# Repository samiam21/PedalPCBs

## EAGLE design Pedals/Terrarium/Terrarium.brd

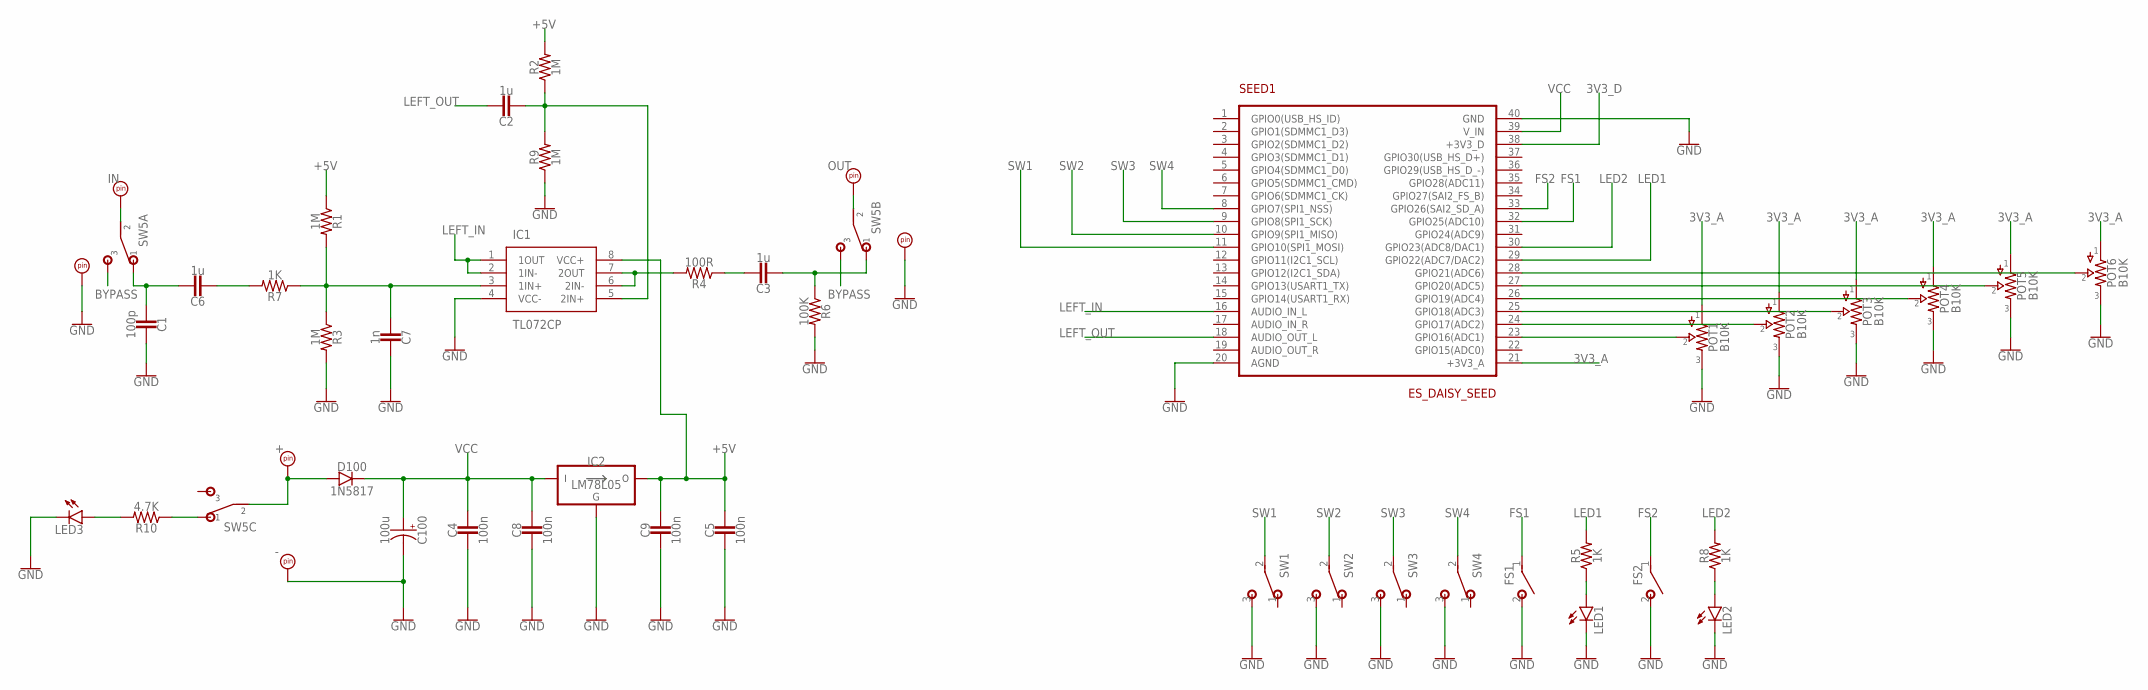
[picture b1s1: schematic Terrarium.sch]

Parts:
C1: 100p; 5MM
C2, C3, C6: 1u; .33UF+
C4, C5, C8, C9: 100n; 5MM
C7: 1n; 5MM
C100: 100u; 050_2.5MM.2
D100: 1N5817; DO41-3
FS1, FS2: SPST
GND: PADRD; UNLABELED
IC1: TL072CP; DIP794W53P254L959H508Q8N
IC2: LM78L05; TO92-
IN: PADRD; UNLABELED
IN_GND: PADRD; UNLABELED
LED1, LED2, LED3: LED.3; 3MM_2
OUT: PADRD; UNLABELED
OUT_GND: PADRD; UNLABELED
POT1, POT2, POT3, POT4, POT5, POT6: B10K; 16MM_PADS.2
PWR: PADRD; UNLABELED
R1, R2, R3, R9: 1M; 7.5MM.2
R4: 100R; 7.5MM.2
R5, R7, R8: 1K; 7.5MM.2
R6: 100K; 7.5MM.2
R10: 4.7K; 7.5MM.2
SEED1: ES_DAISY_SEED
SW1, SW2, SW3, SW4: SPDT.1; SPDT_SOLDER_LUG
SW5: 3PDTTOGGLE; 3PDT2

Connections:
3V3_A: POT1.1, POT2.1, POT3.1, POT4.1, POT5.1, POT6.1, SEED1.21 (+3V3_A)
3V3_D: SEED1.38 (+3V3_D)
+5V: C5.1, C9.1, IC1.8 (VCC+), IC2.3 (VO), R1.1, R2.2
BYPASS: SW5.A3 (3), SW5.B3 (3)
FS1: FS1.1, SEED1.32 (GPIO25(ADC10))
FS2: FS2.1, SEED1.33 (GPIO26(SAI2_SD_A))
GND: C1.1, C4.2, C5.2, C7.1, C8.2, C9.2, C100.-, FS1.2 (S), FS2.2 (S), GND.P$1, IC1.4 (VCC-), IC2.2 (GND), IN_GND.P$1, LED1.P$1 (C), LED2.P$1 (C), LED3.P$1 (C), OUT_GND.P$1, POT1.3, POT2.3, POT3.3, POT4.3, POT5.3, POT6.3, R3.2, R6.2, R9.1, SEED1.20 (AGND), SEED1.40 (GND), SW1.3 (S), SW2.3 (S), SW3.3 (S), SW4.3 (S)
LED1: R5.2, SEED1.29 (GPIO22(ADC7/DAC2))
LED2: R8.2, SEED1.30 (GPIO23(ADC8/DAC1))
LEFT_IN: IC1.1 (1OUT), IC1.2 (1IN-), SEED1.16 (AUDIO_IN_L)
LEFT_OUT: C2.1, SEED1.18 (AUDIO_OUT_L)
unnamed: POT1.2, SEED1.23 (GPIO16(ADC1))
unnamed: POT2.2, SEED1.24 (GPIO17(ADC2))
unnamed: POT3.2, SEED1.25 (GPIO18(ADC3))
unnamed: POT4.2, SEED1.26 (GPIO19(ADC4))
unnamed: POT5.2, SEED1.27 (GPIO20(ADC5))
unnamed: POT6.2, SEED1.28 (GPIO21(ADC6))
unnamed: LED1.ANODE (A), R5.1
unnamed: LED2.ANODE (A), R8.1
unnamed: D100.A, PWR.P$1, SW5.C2 (2)
unnamed: C3.1, R4.1
unnamed: C3.2, R6.1, SW5.B1 (1)
unnamed: C1.2, C6.1, SW5.A1 (1)
unnamed: IN.P$1, SW5.A2 (2)
unnamed: IC1.6 (2IN-), IC1.7 (2OUT), R4.2
unnamed: C6.2, R7.2
unnamed: C7.2, IC1.3 (1IN+), R1.2, R3.1, R7.1
unnamed: C2.2, IC1.5 (2IN+), R2.1, R9.2
unnamed: R10.1, SW5.C1 (1)
unnamed: LED3.ANODE (A), R10.2
unnamed: OUT.P$1, SW5.B2 (2)
SW1: SEED1.11 (GPIO10(SPI1_MOSI)), SW1.2
SW2: SEED1.10 (GPIO9(SPI1_MISO)), SW2.2
SW3: SEED1.9 (GPIO8(SPI1_SCK)), SW3.2
SW4: SEED1.8 (GPIO7(SPI1_NSS)), SW4.2
VCC: C4.1, C8.1, C100.+, D100.C, IC2.1 (VI), SEED1.39 (V_IN)

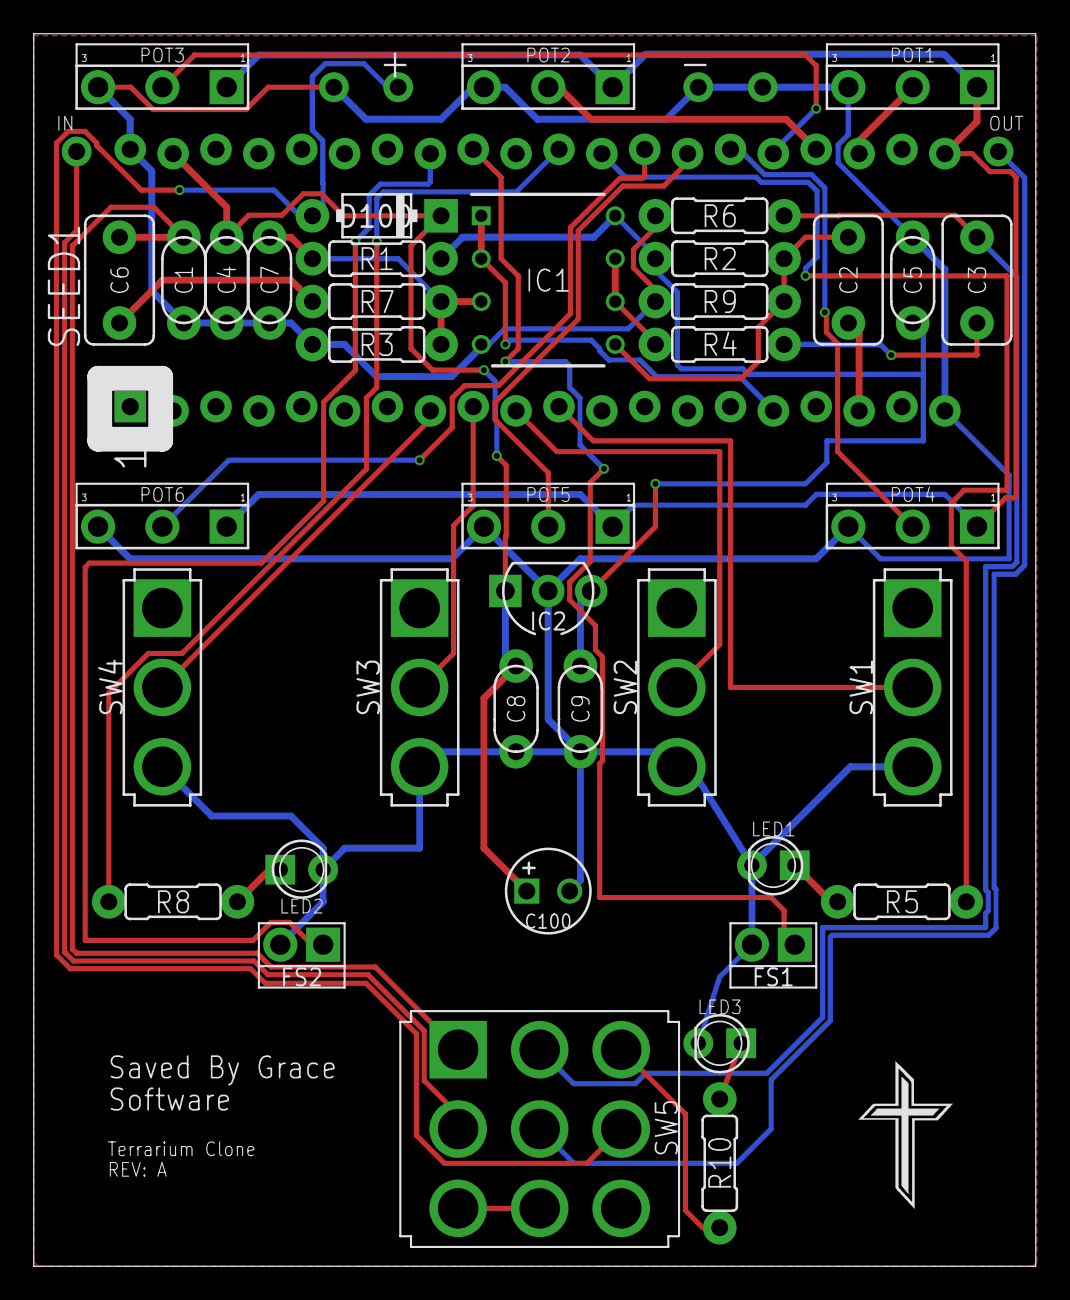
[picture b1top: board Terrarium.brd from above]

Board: 2 copper layers, 59.4 x 73.0 mm, 46 parts (0 on the bottom side), 35 nets.

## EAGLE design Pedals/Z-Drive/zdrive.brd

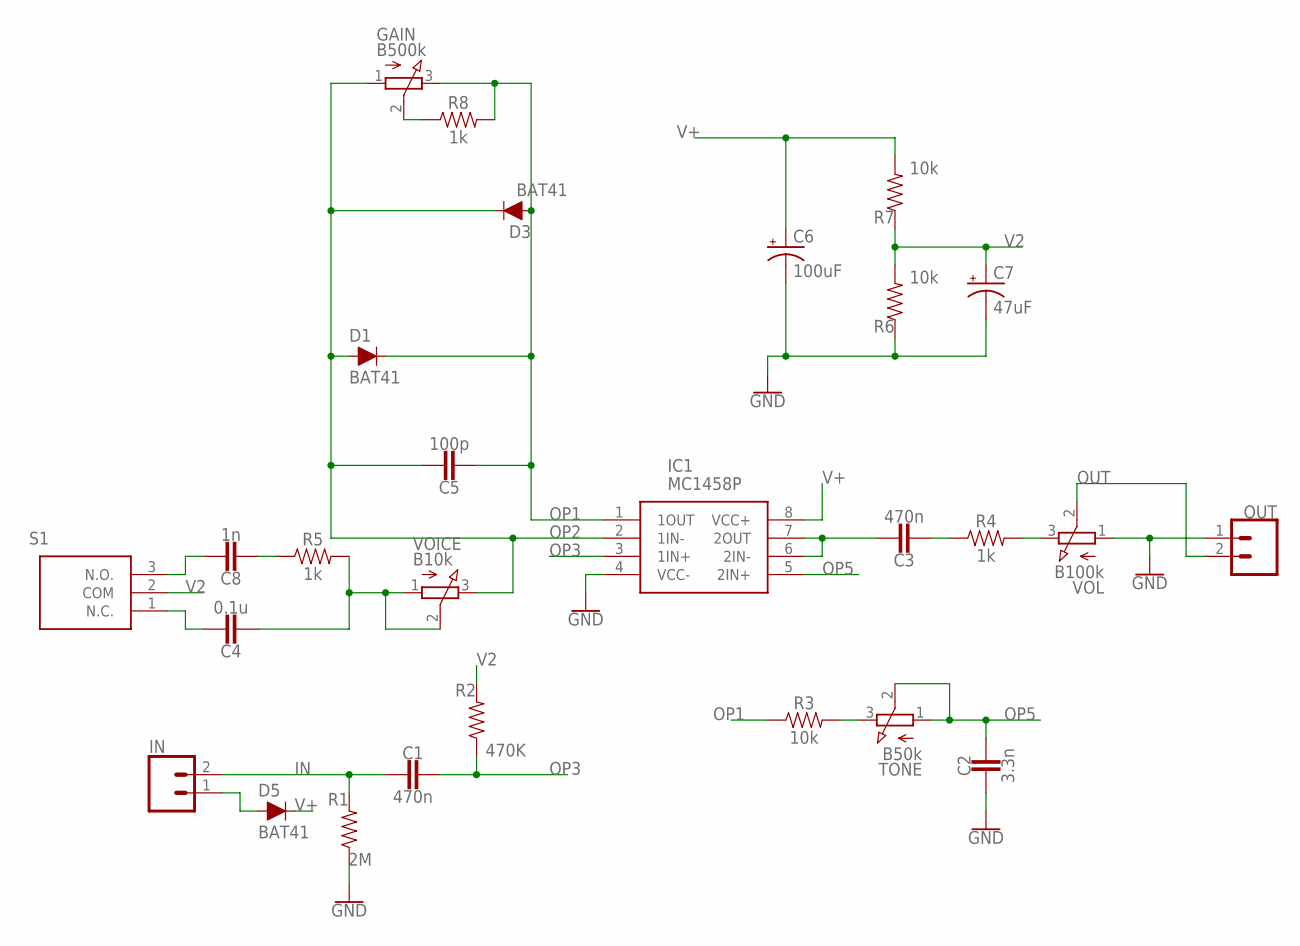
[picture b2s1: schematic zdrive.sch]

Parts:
C1, C3: 470n; .33UF+
C2: 3.3n; .33UF+
C4: 0.1u; .33UF+
C5: 100p; .33UF+
C6: 100uF; CPOL-RADIAL-2.5MM-6.5MM
C7: 47uF; CPOL-RADIAL-2.5MM-6.5MM
C8: 1n; .33UF+
D1, D3, D5: BAT41; DIODE-1N4001-KIT
GAIN: B500k; 3RP/1610N
IC1: MC1458P; DIP794W53P254L959H508Q8N
IN: CONN_02; 1X02
OUT: CONN_02; 1X02
R1: 2M; AXIAL-0.3
R2: 470K; AXIAL-0.3
R3, R6, R7: 10k; AXIAL-0.3
R4, R5, R8: 1k; AXIAL-0.3
S1: 100SP1T1B2M2QE; 100SP1T1B4M2QE
TONE: B50k; 3RP/1610N
VOICE: B10k; 3RP/1610N
VOL: B100k; 3RP/1610N

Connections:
9V: D5.A, IN.1
GND: C2.2, C6.2 (-), C7.2 (-), IC1.4 (VCC-), OUT.1, R1.P$1 (1), R6.P$1 (1), VOL.1 (A)
IN: C1.2, IN.2, R1.P$2 (2)
unnamed: R3.P$2 (2), TONE.3 (E)
unnamed: C3.1, IC1.6 (2IN-), IC1.7 (2OUT)
unnamed: C3.2, R4.P$1 (1)
unnamed: R4.P$2 (2), VOL.3 (E)
unnamed: GAIN.2 (S), R8.P$1 (1)
unnamed: C8.2, R5.P$1 (1)
unnamed: C4.1, S1.1 (N.C.)
unnamed: C8.1, S1.3 (N.O.)
unnamed: C4.2, R5.P$2 (2), VOICE.1 (A), VOICE.2 (S)
OP1: C5.2, D1.C, D3.A, GAIN.3 (E), IC1.1 (1OUT), R3.P$1 (1), R8.P$2 (2)
OP2: C5.1, D1.A, D3.C, GAIN.1 (A), IC1.2 (1IN-), VOICE.3 (E)
OP3: C1.1, IC1.3 (1IN+), R2.P$1 (1)
OP5: C2.1, IC1.5 (2IN+), TONE.1 (A), TONE.2 (S)
OUT: OUT.2, VOL.2 (S)
V2: C7.1 (+), R2.P$2 (2), R6.P$2 (2), R7.P$1 (1), S1.2 (COM)
V+: C6.1 (+), D5.C, IC1.8 (VCC+), R7.P$2 (2)

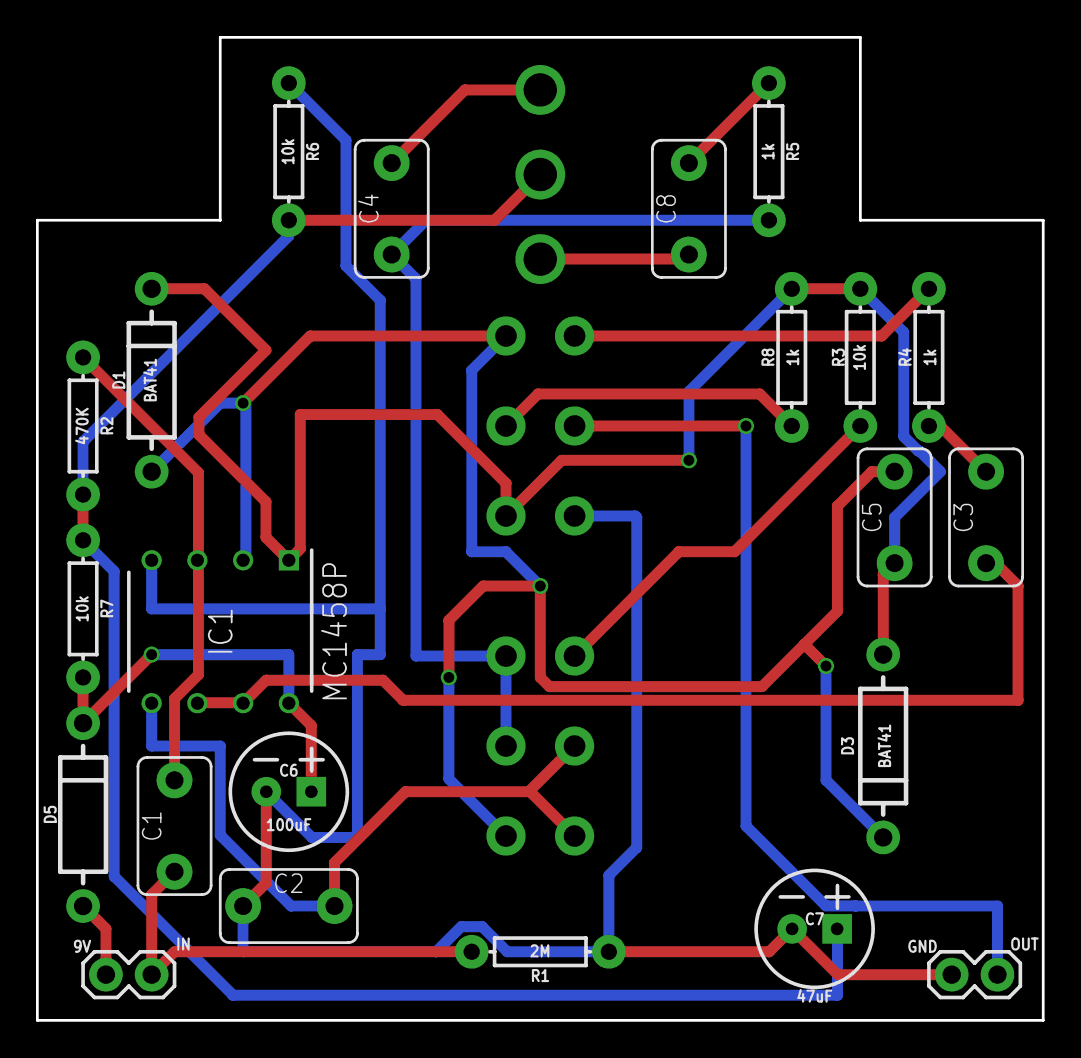
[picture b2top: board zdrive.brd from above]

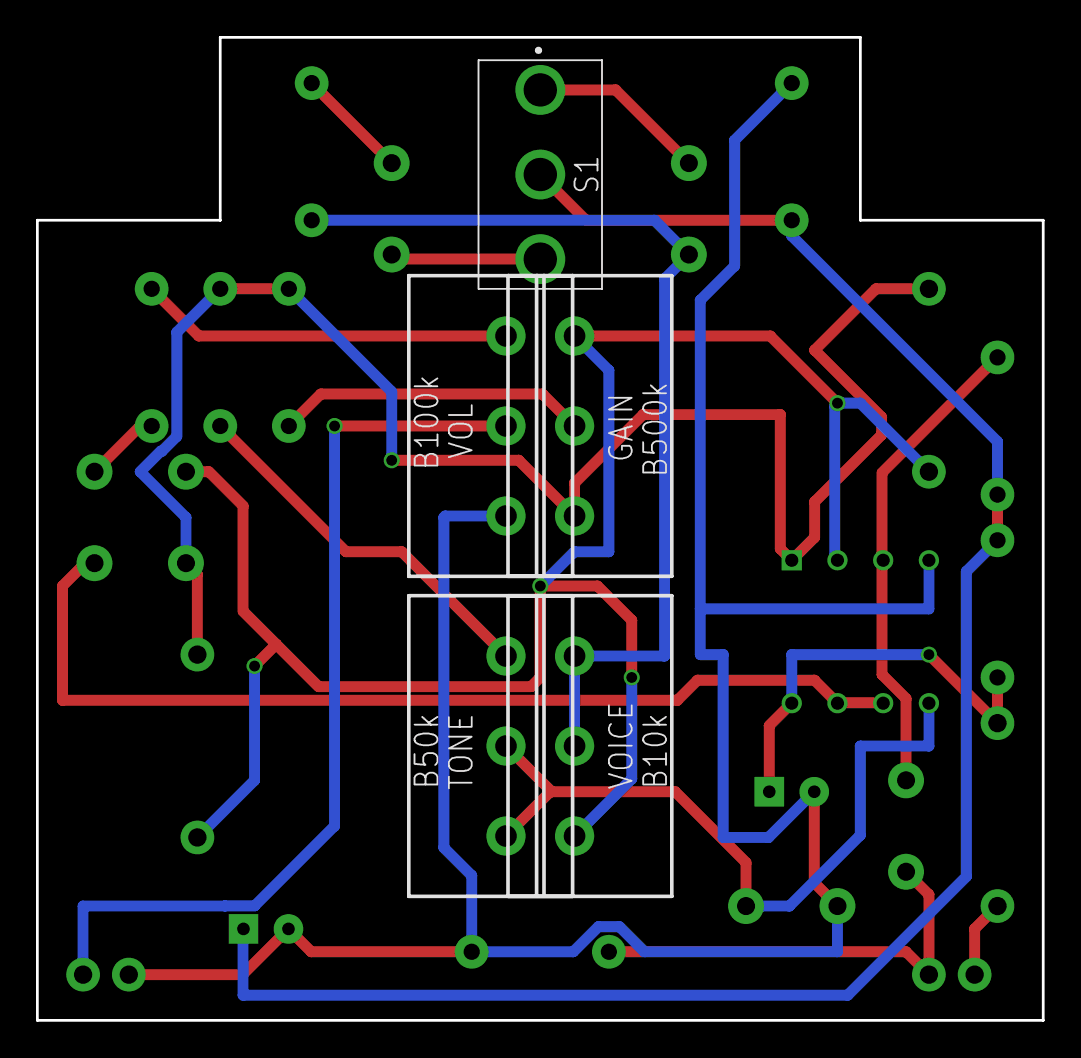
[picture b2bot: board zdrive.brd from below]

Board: 2 copper layers, 55.9 x 54.6 mm, 27 parts (5 on the bottom side), 19 nets.

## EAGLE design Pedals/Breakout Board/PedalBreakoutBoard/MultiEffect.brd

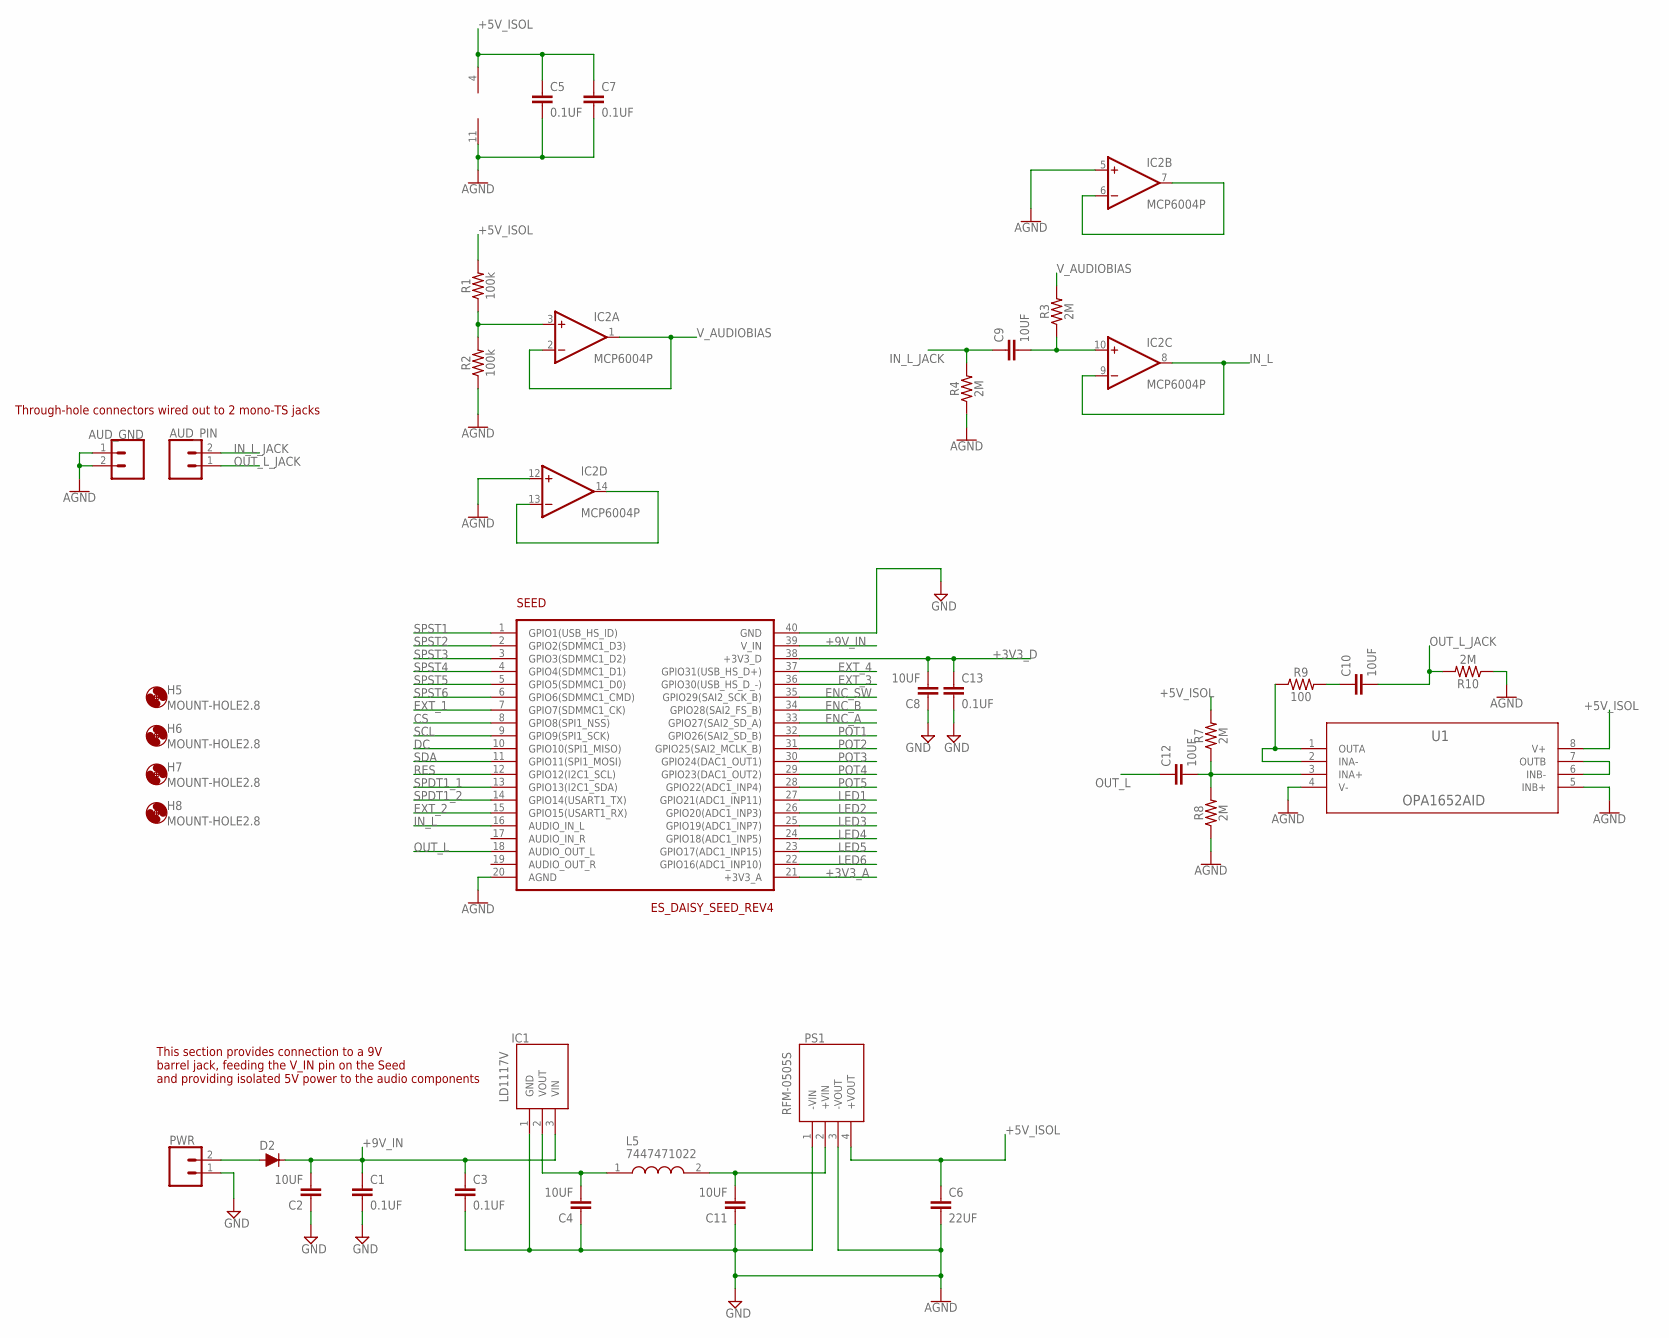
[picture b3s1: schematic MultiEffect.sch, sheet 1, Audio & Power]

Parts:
AUD_GND: CONN_02; 1X02
AUD_PIN: CONN_02; 1X02
C1, C3, C5, C7, C13: 0.1UF; CAP-PTH-SMALL-KIT
C2, C4, C8, C9, C10, C11, C12: 10UF; CAP-PTH-SMALL-KIT
C6: 22UF; CAP-PTH-SMALL-KIT
D2: 200mA/100V/1V; DIODE-1N4148
H5, H6, H7, H8: MOUNT-HOLE2.8; 2,8
IC1: LD1117V; TO255P460X1020X2008-3P
IC2: MCP6004P; DIL14
L5: 7447471022; WE-TIS_111190
PS1: RFM-0505S; RFM0505S
PWR: CONN_02; 1X02
R1, R2: 100k; AXIAL-0.3
R3, R4, R7, R8, R10: 2M; AXIAL-0.3
R9: 100; AXIAL-0.3
SEED: ES_DAISY_SEED_REV4; ES_DAISY_SEED
U1: OPA1652AID; D8

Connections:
+3V3_A: SEED.21 (+3V3_A); also elsewhere on the board
+3V3_D: C8.2, C13.1, SEED.38 (+3V3_D); also elsewhere on the board
+5V_ISOL: C5.1, C6.1, C7.1, IC2.4 (V+), PS1.4 (+VOUT), R1.P$2 (2), R7.P$2 (2), U1.8 (V+)
+9V_IN: C1.1, C2.2, C3.1, D2.C, IC1.3 (VIN), SEED.39 (V_IN)
AGND: AUD_GND.1, AUD_GND.2, C5.2, C7.2, IC2.5 (+IN), IC2.11 (V-), IC2.12 (+IN), R2.P$1 (1), R4.P$1 (1), R8.P$1 (1), R10.P$1 (1), SEED.20 (AGND), U1.4 (V-), U1.5 (INB+)
CS: SEED.8 (GPIO8(SPI1_NSS)); also elsewhere on the board
DC: SEED.10 (GPIO10(SPI1_MISO)); also elsewhere on the board
ENC_A: SEED.33 (GPIO27(SAI2_SD_A)); also elsewhere on the board
ENC_B: SEED.34 (GPIO28(SAI2_FS_B)); also elsewhere on the board
ENC_SW: SEED.35 (GPIO29(SAI2_SCK_B)); also elsewhere on the board
EXT_1: SEED.7 (GPIO7(SDMMC1_CK)); also elsewhere on the board
EXT_2: SEED.15 (GPIO15(USART1_RX)); also elsewhere on the board
EXT_3: SEED.36 (GPIO30(USB_HS_D_-)); also elsewhere on the board
EXT_4: SEED.37 (GPIO31(USB_HS_D+)); also elsewhere on the board
GND: C1.2, C2.1, C3.2, C4.1, C6.2, C8.1, C11.1, C13.2, IC1.1 (GND), PS1.1 (-VIN), PS1.3 (-VOUT), PWR.1, SEED.40 (GND); also elsewhere on the board
IN_L: IC2.8 (OUT), IC2.9 (-IN), SEED.16 (AUDIO_IN_L)
IN_L_JACK: AUD_PIN.2, C9.1, R4.P$2 (2)
LED1: SEED.27 (GPIO21(ADC1_INP11)); also elsewhere on the board
LED2: SEED.26 (GPIO20(ADC1_INP3)); also elsewhere on the board
LED3: SEED.25 (GPIO19(ADC1_INP7)); also elsewhere on the board
LED4: SEED.24 (GPIO18(ADC1_INP5)); also elsewhere on the board
LED5: SEED.23 (GPIO17(ADC1_INP15)); also elsewhere on the board
LED6: SEED.22 (GPIO16(ADC1_INP10)); also elsewhere on the board
unnamed: D2.A, PWR.2
unnamed: IC2.3 (+IN), R1.P$1 (1), R2.P$2 (2)
unnamed: C11.2, L5.2, PS1.2 (+VIN)
unnamed: C4.2, IC1.2 (VOUT), L5.1
unnamed: C9.2, IC2.10 (+IN), R3.P$1 (1)
unnamed: IC2.13 (-IN), IC2.14 (OUT)
unnamed: C12.2, R7.P$1 (1), R8.P$2 (2), U1.3 (INA+)
unnamed: R9.P$1 (1), U1.1 (OUTA), U1.2 (INA-)
unnamed: C10.1, R9.P$2 (2)
unnamed: U1.6 (INB-), U1.7 (OUTB)
unnamed: IC2.6 (-IN), IC2.7 (OUT)
OUT_L: C12.1, SEED.18 (AUDIO_OUT_L)
OUT_L_JACK: AUD_PIN.1, C10.2, R10.P$2 (2)
POT1: SEED.32 (GPIO26(SAI2_SD_B)); also elsewhere on the board
POT2: SEED.31 (GPIO25(SAI2_MCLK_B)); also elsewhere on the board
POT3: SEED.30 (GPIO24(DAC1_OUT1)); also elsewhere on the board
POT4: SEED.29 (GPIO23(DAC1_OUT2)); also elsewhere on the board
POT5: SEED.28 (GPIO22(ADC1_INP4)); also elsewhere on the board
RES: SEED.12 (GPIO12(I2C1_SCL)); also elsewhere on the board
SCL: SEED.9 (GPIO9(SPI1_SCK)); also elsewhere on the board
SDA: SEED.11 (GPIO11(SPI1_MOSI)); also elsewhere on the board
SPDT1_1: SEED.13 (GPIO13(I2C1_SDA)); also elsewhere on the board
SPDT1_2: SEED.14 (GPIO14(USART1_TX)); also elsewhere on the board
SPST1: SEED.1 (GPIO1(USB_HS_ID)); also elsewhere on the board
SPST2: SEED.2 (GPIO2(SDMMC1_D3)); also elsewhere on the board
SPST3: SEED.3 (GPIO3(SDMMC1_D2)); also elsewhere on the board
SPST4: SEED.4 (GPIO4(SDMMC1_D1)); also elsewhere on the board
SPST5: SEED.5 (GPIO5(SDMMC1_D0)); also elsewhere on the board
SPST6: SEED.6 (GPIO6(SDMMC1_CMD)); also elsewhere on the board
V_AUDIOBIAS: IC2.1 (OUT), IC2.2 (-IN), R3.P$2 (2)

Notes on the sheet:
Through-hole connectors wired out to 2 mono-TS jacks
This section provides connection to a 9V barrel jack, feeding the V_IN pin on the Seed and providing isolated 5V power to the audio components

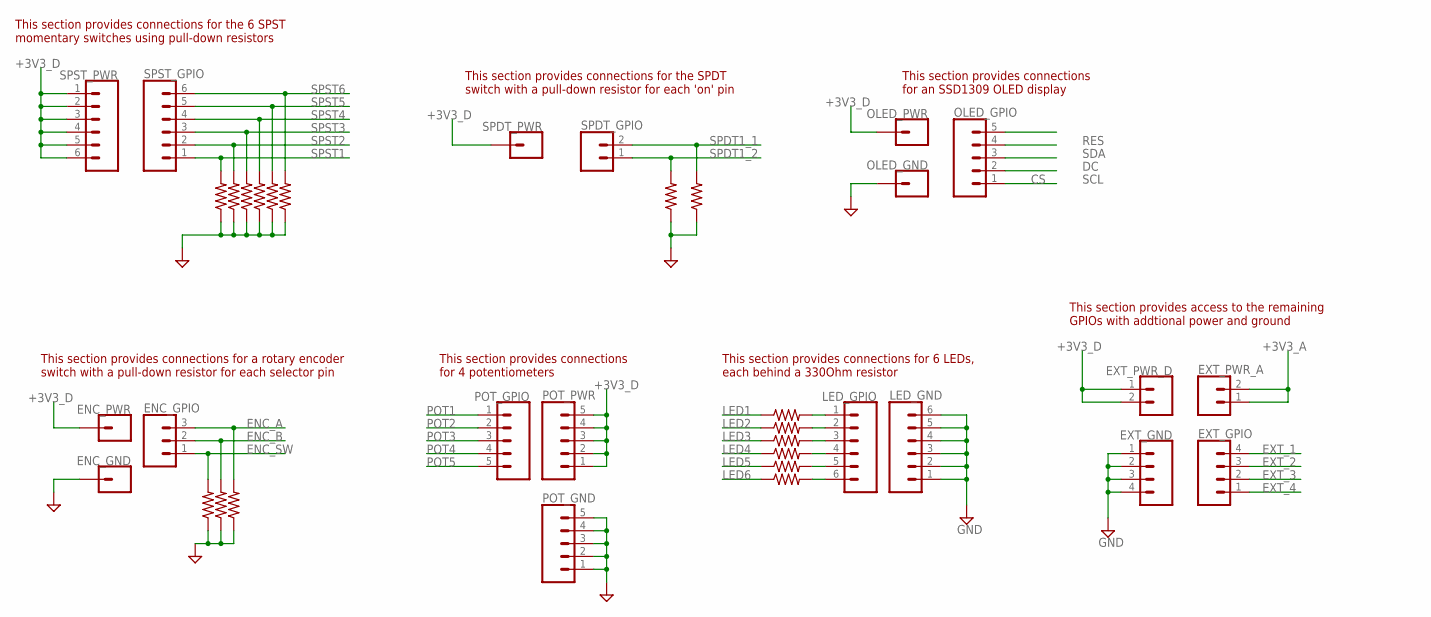
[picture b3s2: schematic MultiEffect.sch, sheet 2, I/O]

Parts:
D11, D12: 10k; AXIAL-0.3
ENC_GND: CONN_01; 1X01
ENC_GPIO: CONN_03; 1X03
ENC_PWR: CONN_01; 1X01
EXT_GND: CONN_04; 1X04
EXT_GPIO: CONN_04; 1X04
EXT_PWR_A: CONN_02; 1X02
EXT_PWR_D: CONN_02; 1X02
H2, H3, H4: 10k; AXIAL-0.3
L1, L2, L3, L4, L6, L7: 330; AXIAL-0.3
LED_GND: CONN_06SILK_FEMALE_PTH; 1X06
LED_GPIO: CONN_06SILK_FEMALE_PTH; 1X06
OLED_GND: CONN_01; 1X01
OLED_GPIO: CONN_05; 1X05
OLED_PWR: CONN_01; 1X01
POT_GND: CONN_05; 1X05
POT_GPIO: CONN_05; 1X05
POT_PWR: CONN_05; 1X05
S1, S2, S3, S4, S5, S6: 10k; AXIAL-0.3
SPDT_GPIO: CONN_02; 1X02
SPDT_PWR: CONN_01; 1X01
SPST_GPIO: CONN_06SILK_FEMALE_PTH; 1X06
SPST_PWR: CONN_06SILK_FEMALE_PTH; 1X06

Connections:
+3V3_A: EXT_PWR_A.1, EXT_PWR_A.2; also elsewhere on the board
+3V3_D: ENC_PWR.1, EXT_PWR_D.1, EXT_PWR_D.2, OLED_PWR.1, POT_PWR.1, POT_PWR.2, POT_PWR.3, POT_PWR.4, POT_PWR.5, SPDT_PWR.1, SPST_PWR.1, SPST_PWR.2, SPST_PWR.3, SPST_PWR.4, SPST_PWR.5, SPST_PWR.6; also elsewhere on the board
CS: OLED_GPIO.1; also elsewhere on the board
DC: OLED_GPIO.3; also elsewhere on the board
ENC_A: ENC_GPIO.3, H4.P$2 (2); also elsewhere on the board
ENC_B: ENC_GPIO.2, H3.P$2 (2); also elsewhere on the board
ENC_SW: ENC_GPIO.1, H2.P$2 (2); also elsewhere on the board
EXT_1: EXT_GPIO.4; also elsewhere on the board
EXT_2: EXT_GPIO.3; also elsewhere on the board
EXT_3: EXT_GPIO.2; also elsewhere on the board
EXT_4: EXT_GPIO.1; also elsewhere on the board
GND: D11.P$1 (1), D12.P$1 (1), ENC_GND.1, EXT_GND.1, EXT_GND.2, EXT_GND.3, EXT_GND.4, H2.P$1 (1), H3.P$1 (1), H4.P$1 (1), LED_GND.1, LED_GND.2, LED_GND.3, LED_GND.4, LED_GND.5, LED_GND.6, OLED_GND.1, POT_GND.1, POT_GND.2, POT_GND.3, POT_GND.4, POT_GND.5, S1.P$1 (1), S2.P$1 (1), S3.P$1 (1), S4.P$1 (1), S5.P$1 (1), S6.P$1 (1); also elsewhere on the board
LED1: L1.P$1 (1); also elsewhere on the board
LED2: L2.P$1 (1); also elsewhere on the board
LED3: L3.P$1 (1); also elsewhere on the board
LED4: L4.P$1 (1); also elsewhere on the board
LED5: L6.P$1 (1); also elsewhere on the board
LED6: L7.P$1 (1); also elsewhere on the board
unnamed: L1.P$2 (2), LED_GPIO.1
unnamed: L2.P$2 (2), LED_GPIO.2
unnamed: L3.P$2 (2), LED_GPIO.3
unnamed: L4.P$2 (2), LED_GPIO.4
unnamed: L6.P$2 (2), LED_GPIO.5
unnamed: L7.P$2 (2), LED_GPIO.6
POT1: POT_GPIO.1; also elsewhere on the board
POT2: POT_GPIO.2; also elsewhere on the board
POT3: POT_GPIO.3; also elsewhere on the board
POT4: POT_GPIO.4; also elsewhere on the board
POT5: POT_GPIO.5; also elsewhere on the board
RES: OLED_GPIO.5; also elsewhere on the board
SCL: OLED_GPIO.2; also elsewhere on the board
SDA: OLED_GPIO.4; also elsewhere on the board
SPDT1_1: D11.P$2 (2), SPDT_GPIO.2; also elsewhere on the board
SPDT1_2: D12.P$2 (2), SPDT_GPIO.1; also elsewhere on the board
SPST1: S1.P$2 (2), SPST_GPIO.1; also elsewhere on the board
SPST2: S2.P$2 (2), SPST_GPIO.2; also elsewhere on the board
SPST3: S3.P$2 (2), SPST_GPIO.3; also elsewhere on the board
SPST4: S4.P$2 (2), SPST_GPIO.4; also elsewhere on the board
SPST5: S5.P$2 (2), SPST_GPIO.5; also elsewhere on the board
SPST6: S6.P$2 (2), SPST_GPIO.6; also elsewhere on the board

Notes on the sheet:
This section provides connections for the SPDT switch with a pull-down resistor for each 'on' pin
This section provides connections for a rotary encoder switch with a pull-down resistor for each selector pin
This section provides connections for 4 potentiometers
This section provides connections for the 6 SPST momentary switches using pull-down resistors
This section provides connections for 6 LEDs, each behind a 330Ohm resistor
This section provides connections for an SSD1309 OLED display
This section provides access to the remaining GPIOs with addtional power and ground

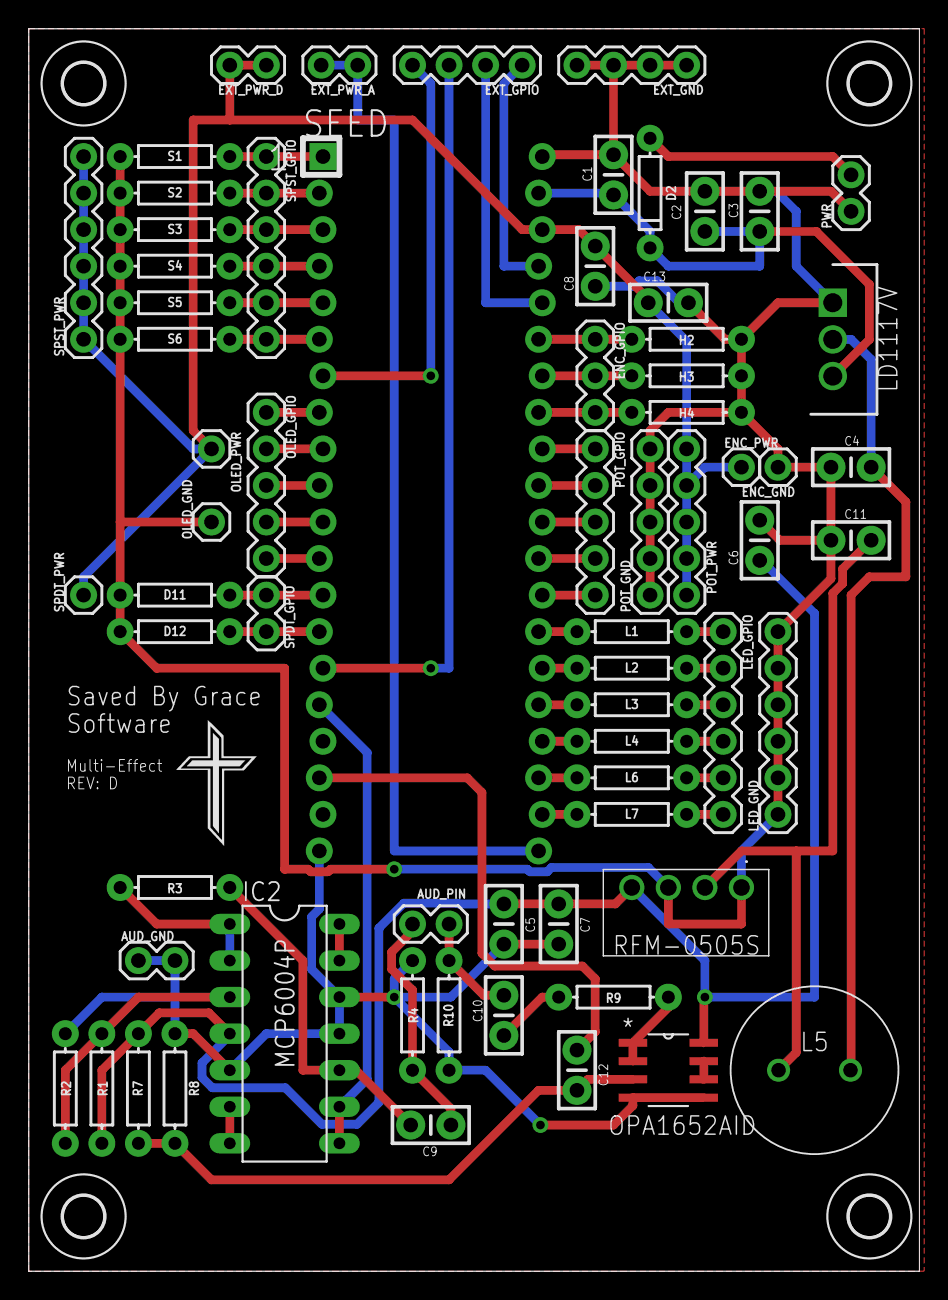
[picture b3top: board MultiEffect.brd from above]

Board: 2 copper layers, 61.9 x 86.3 mm, 71 parts (0 on the bottom side), 59 nets.

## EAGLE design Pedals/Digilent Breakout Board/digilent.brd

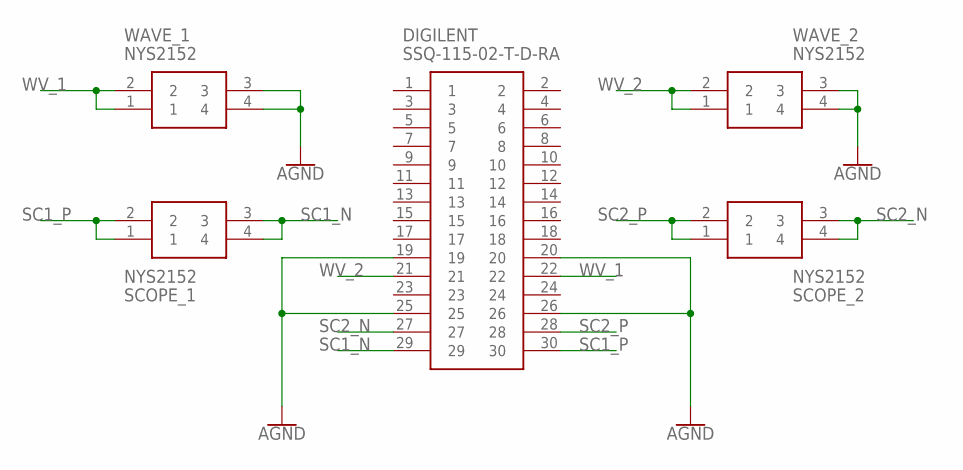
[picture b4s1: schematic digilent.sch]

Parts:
DIGILENT: SSQ-115-02-T-D-RA; RHDRRA30W64P254_2X15_3861X851X
SCOPE_1, SCOPE_2: NYS2152
WAVE_1, WAVE_2: NYS2152

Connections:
AGND: DIGILENT.19, DIGILENT.20, DIGILENT.25, DIGILENT.26, WAVE_1.3, WAVE_1.4, WAVE_2.3, WAVE_2.4
SC1_N: DIGILENT.29, SCOPE_1.3, SCOPE_1.4
SC1_P: DIGILENT.30, SCOPE_1.1, SCOPE_1.2
SC2_N: DIGILENT.27, SCOPE_2.3, SCOPE_2.4
SC2_P: DIGILENT.28, SCOPE_2.1, SCOPE_2.2
WV_1: DIGILENT.22, WAVE_1.1, WAVE_1.2
WV_2: DIGILENT.21, WAVE_2.1, WAVE_2.2

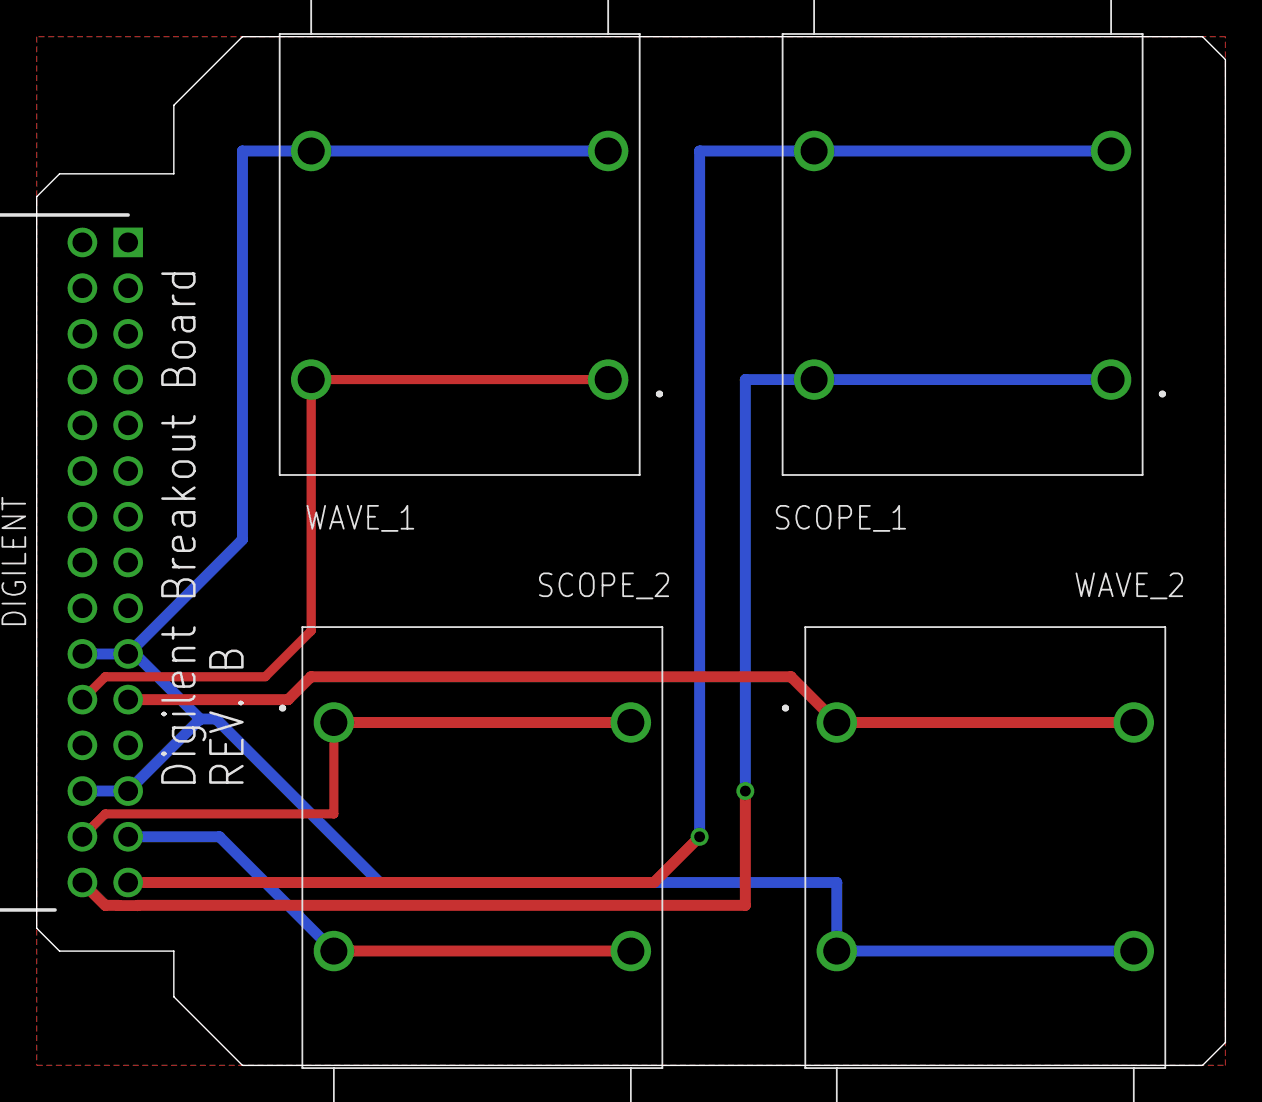
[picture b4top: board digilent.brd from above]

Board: 2 copper layers, 66.0 x 57.1 mm, 5 parts (0 on the bottom side), 7 nets.

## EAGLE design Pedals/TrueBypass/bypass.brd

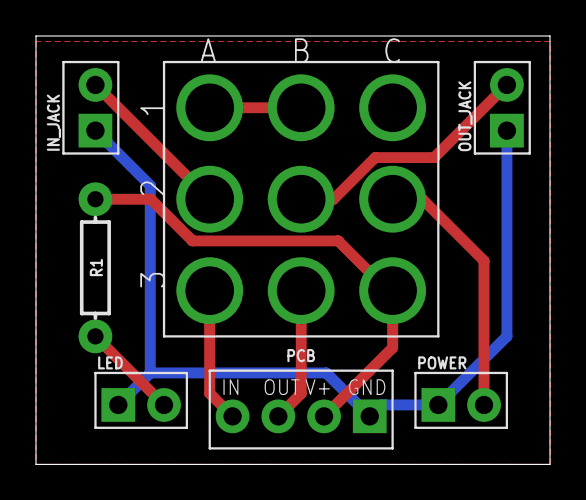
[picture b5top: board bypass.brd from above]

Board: 2 copper layers, 28.6 x 23.8 mm, 7 parts (0 on the bottom side), 9 nets.

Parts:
IN_JACK: MOLEX-1X2
LED: MOLEX-1X2
OUT_JACK: MOLEX-1X2
PCB: MOLEX-1X4
POWER: MOLEX-1X2
R1: 330; AXIAL-0.3
SW1: 3PDT

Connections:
AGND: IN_JACK.1, LED.1, OUT_JACK.1, PCB.1, POWER.1
unnamed: IN_JACK.2, SW1.A2
unnamed: OUT_JACK.2, SW1.B2
unnamed: SW1.A1, SW1.B1
unnamed: PCB.2, R1.P$1, SW1.C3
unnamed: PCB.4, SW1.A3
unnamed: PCB.3, SW1.B3
unnamed: POWER.2, SW1.C2
unnamed: LED.2, R1.P$2

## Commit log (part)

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2021-03-31 Add eagle libraries and initial zdrive
2021-03-31 Update zdrive schematic with new pots
2021-03-31 Add zdrive reference docs
2021-03-31 Update schematic and begin board layout
2021-03-31 Working on layout
2021-04-01 Remove accidental folder commit
2021-04-01 Adding switch for capacitor
2021-04-01 Working on board layout
2021-04-07 Restarting board design...
2021-04-07 Re-add reference docs
2021-04-13 Working on routing
2021-04-13 Board routed V1
2021-04-15 Shift switch
2021-04-16 Adjusted the pots
2021-04-19 Rotate switch
2021-04-22 Shift pots so they are centered
2021-04-22 Update silkscreen
2021-04-28 Add bypass schematic
2021-04-28 Route board
2021-05-10 Update switch to correct footprint size
2021-05-11 Switch pots to bottom and add gnd plane
2021-05-12 Flip top pots
2021-05-12 Flip bottom pots
2021-05-12 Push to Fusion
2021-06-11 Flipped the volume and tone pots
2021-06-11 Fix labels on board
2021-06-11 Move resistor for greater impact of switch
2021-07-27 Add parts to library
2021-07-27 Add digilent schematic
2021-07-27 Add grounding planes
2021-07-27 Round corners
2021-07-27 Update board label
2021-08-17 Add Analog Discovery 2 header to library
2021-08-23 DP-97 - Move breakout board to this repo
2021-08-23 DP-97 - Update with wave analysis board
2021-08-23 DP-97 - Add DIP switch to library
2021-09-29 Put correct header on the digilent PCB
2021-09-29 DP-97 - Update multi-effect grounding scheme
2021-09-29 DP-97 - Finish updating grounding scheme on multi-effect pedal
2021-10-06 DP-97 - Add power conditioning caps to 3V3_D
2023-03-11 Updated to larger cap footprints for Headmaster
2023-03-27 Removed transistors
2023-03-29 Add Electrosmith library
2023-03-29 Add more libraries
2023-03-29 Start Terrarium schematic
2023-04-03 Updating schematic
2023-04-03 Finish base schematic
2023-04-03 Begin board layout
2023-04-03 Fix capacitor sizes
2023-04-04 Update parts and place them on the board
2023-04-04 Finished terrarium board routing
2023-04-05 Add true bypass
2023-04-05 Add the Terrarium PDF
2023-04-11 Revert headmaster to correct revision
2023-04-11 Update capacitors to be larger size
2023-05-08 Fix true bypass circuit on Terrarium
2023-05-08 Fix silkscreen on Terrarium

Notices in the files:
parts and their libraries:
SparkFun-Connectors: Licensing: Creative Commons ShareAlike 4.0 International - https://creativecommons.org/licenses/by-sa/4.0
